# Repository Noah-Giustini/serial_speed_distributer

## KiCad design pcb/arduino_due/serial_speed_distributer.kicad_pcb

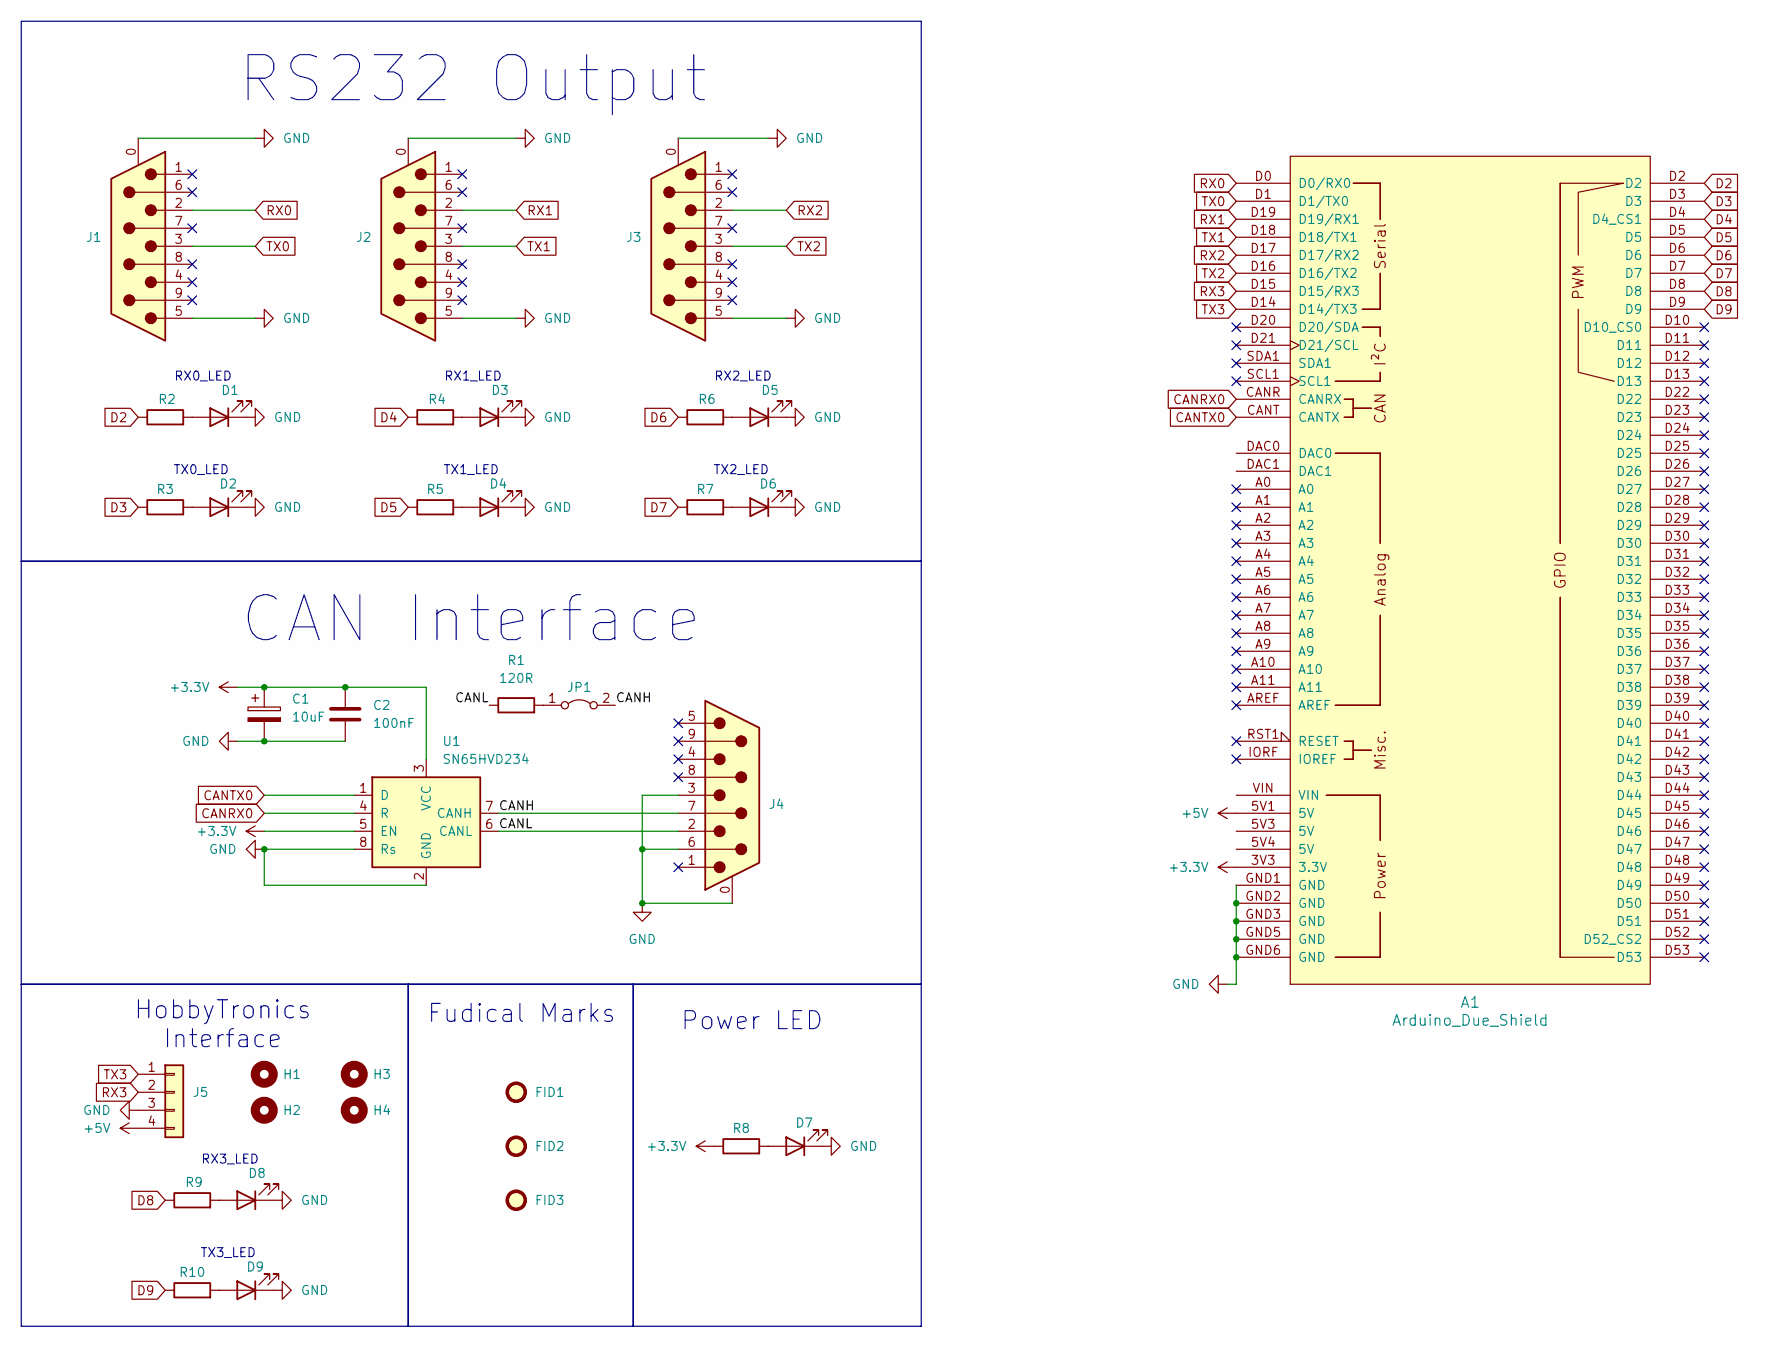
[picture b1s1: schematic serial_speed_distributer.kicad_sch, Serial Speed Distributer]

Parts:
A1: Arduino_Due_Shield
C1: 10uF; C_Disc_D5.1mm_W3.2mm_P5.00mm
C2: 100nF; C_Disc_D5.0mm_W2.5mm_P5.00mm
D1, D3, D5, D8: LED_GRN; LED_D3.0mm
D2, D4, D6, D9: LED_ORNG; LED_D3.0mm
D7: LED_RED; LED_D3.0mm
FID1, FID2, FID3: Fiducial; Fiducial_0.5mm_Mask1mm
H1, H2, H3, H4: MountingHole; MountingHole_3.2mm_M3_DIN965_Pad
J1, J2, J3, J4: DE9_Plug_MountingHoles; DSUB-9_Male_Vertical_P2.77x2.84mm_MountingHoles
J5: HobbyTronics UART Interface; PinHeader_1x04_P2.54mm_Vertical
JP1: Jumper_2_Bridged; PinHeader_1x02_P2.54mm_Vertical
R1: 120R; R_Axial_DIN0207_L6.3mm_D2.5mm_P7.62mm_Horizontal
R2, R3, R4, R5, R6, R7, R8, R9, R10: 220R; R_Axial_DIN0207_L6.3mm_D2.5mm_P7.62mm_Horizontal
U1: SN65HVD234; SOIC-8_3.9x4.9mm_P1.27mm

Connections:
+3.3V: A1.3V3 (3.3V), C1.1, C2.1, R8.1, U1.3 (VCC), U1.5 (EN)
+5V: A1.5V1 (5V), J5.4
/CANH: J4.7, JP1.2 (B), U1.7 (CANH)
/CANL: J4.2, R1.1, U1.6 (CANL)
CANRX0: A1.CANR (CANRX), U1.4 (R)
CANTX0: A1.CANT (CANTX), U1.1 (D)
D2: A1.D2, R2.1
D3: A1.D3, R3.1
D4: A1.D4 (D4_CS1), R4.1
D5: A1.D5, R5.1
D6: A1.D6, R6.1
D7: A1.D7, R7.1
D8: A1.D8, R9.1
D9: A1.D9, R10.1
GND: A1.GND1 (GND), A1.GND2 (GND), A1.GND3 (GND), A1.GND5 (GND), A1.GND6 (GND), C1.2, C2.2, D1.1 (K), D2.1 (K), D3.1 (K), D4.1 (K), D5.1 (K), D6.1 (K), D7.1 (K), D8.1 (K), D9.1 (K), J1.0 (PAD), J1.5, J2.0 (PAD), J2.5, J3.0 (PAD), J3.5, J4.0 (PAD), J4.3, J4.6, J5.3, U1.2 (GND), U1.8 (Rs)
unnamed: D1.2 (A), R2.2
unnamed: D2.2 (A), R3.2
unnamed: D3.2 (A), R4.2
unnamed: D4.2 (A), R5.2
unnamed: D5.2 (A), R6.2
unnamed: D6.2 (A), R7.2
unnamed: D7.2 (A), R8.2
unnamed: D8.2 (A), R9.2
unnamed: D9.2 (A), R10.2
unnamed: JP1.1 (A), R1.2
RX0: A1.D0 (D0/RX0), J1.2
RX1: A1.D19 (D19/RX1), J2.2
RX2: A1.D17 (D17/RX2), J3.2
RX3: A1.D15 (D15/RX3), J5.2
TX0: A1.D1 (D1/TX0), J1.3
TX1: A1.D18 (D18/TX1), J2.3
TX2: A1.D16 (D16/TX2), J3.3
TX3: A1.D14 (D14/TX3), J5.1

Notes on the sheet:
CAN Interface
TX1_LED
RX2_LED
RX0_LED
TX0_LED
Power LED
Fudical Marks
RS232 Output
RX1_LED
TX2_LED
HobbyTronics Interface
RX3_LED
TX3_LED

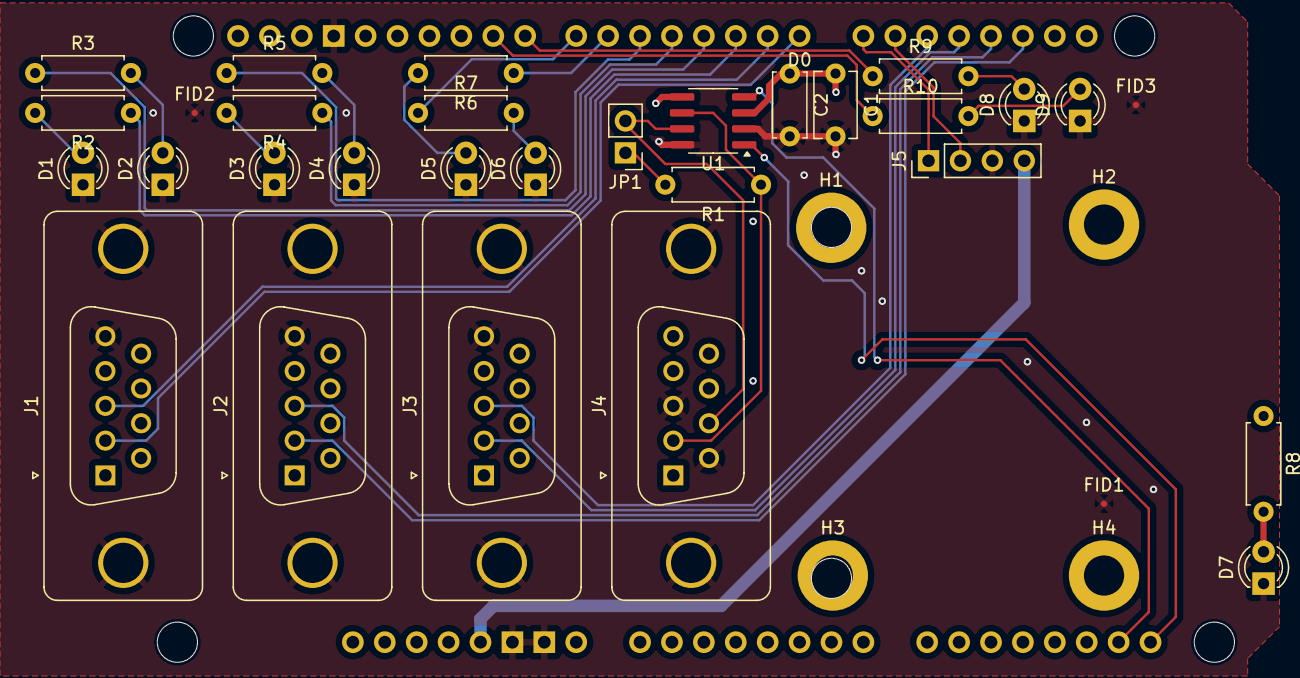
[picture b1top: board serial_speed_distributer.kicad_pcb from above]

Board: 4 copper layers, 36 parts (0 on the bottom side), 33 nets.

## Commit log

2026-02-24 initial PCB version
2026-03-07 move pcb files to new directory, make directory for teensy
2026-03-07 make directories for teensy and firmware
2026-03-12 initial firmware for arduino, esp and teensy4.1
2026-03-12 adding test string to teensy readme
